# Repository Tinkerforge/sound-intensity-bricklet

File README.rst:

Sound Intensity Bricklet
========================

This repository contains the firmware source code and the hardware design
files. The documentation generator configs can be found at
https://github.com/Tinkerforge/generators

Repository Content
------------------

software/:
 * examples/: Examples for all supported languages
 * build/: Compiled files
 * src/: Source code of firmware
 * Makefile: Makefile to build project

hardware/:
 * Contains KiCad project files and additionally schematics as PDF

datasheets/:
 * Contains datasheets for sensors and complex ICs that are used

Hardware
--------

The hardware is designed with the open source EDA Suite KiCad
(http://www.kicad.org). Before you are able to open the files,
you have to install the Tinkerforge kicad-libraries
(https://github.com/Tinkerforge/kicad-libraries). You can either clone
them directly in hardware/ or clone them in a separate folder and
symlink them into hardware/
(ln -s kicad_path/kicad-libraries project_path/hardware). After that you
can open the .pro file in hardware/ with KiCad and from there view and
modify the schematics and the PCB layout.

Software
--------

If you want to do your own Brick/Bricklet firmware development we highly
recommend that you use our build environment setup script and read the
tutorial (https://www.tinkerforge.com/en/doc/Tutorials/Tutorial_Build_Environment/Tutorial.html).

To compile the C code we recommend you to install the newest GNU Arm Embedded
Toolchain (https://launchpad.net/gcc-arm-embedded/+download).
You also need to install bricklib (https://github.com/Tinkerforge/bricklib)
and brickletlib (https://github.com/Tinkerforge/brickletlib).

You can either clone it directly in software/src/ or clone it in a
separate folder and symlink it into software/src/
(ln -s bricklib_path/bricklib project_path/software/src/ and
ln -s brickletlib_path/brickletlib project_path/software/src/).
Finally make sure to have CMake installed
(http://www.cmake.org/cmake/resources/software.html).

After that you can build the firmware by invoking make in software/.
The firmware (.bin) can then be found in software/build/ and uploaded
with brickv (click button "Flashing" on start screen).

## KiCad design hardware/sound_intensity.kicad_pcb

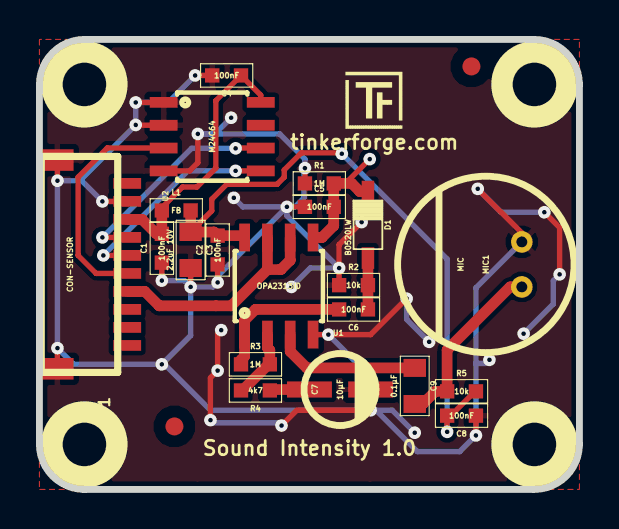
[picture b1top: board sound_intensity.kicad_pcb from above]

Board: 2 copper layers, 30.0 x 25.0 mm, 28 parts (0 on the bottom side), 14 nets.

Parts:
C1, C2, C4, C5, C6, C8: 100nF; 0603
C3: 2.2uF 10V; 0805
C7: 10µF; ELKO_43
C9: 0.1µF; 0805
D1: B0520LW; SOD-123
Fiducial_Mark: VAL**; Fiducial_Mark
Fiducial_Mark#2: VAL**; Fiducial_Mark
L1: FB; 0603
MIC1: MIC; MICRO_9_7
P1: CON-SENSOR
R1, R3: 1M; 0603
R2, R5: 10k; 0603
R4: 4k7; 0603
U1: OPA2313ID; SOIC8
U2: M24C64; SOIC8
U3, U4, U5, U6: DRILL; DRILL_NP
VAL: CE_5mm
VAL#2: WEEE_7mm

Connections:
GND: C1.1, C2.1, C3.2, C4.2, C5.1, C7.2, C8.1, MIC1.2, P1.2, P1.EP, R1.1, R2.1, U1.4, U2.1, U2.2, U2.4
unnamed: C9.2, MIC1.1, R5.1
unnamed: R3.2, R4.2, U1.2
unnamed: C7.1, R4.1
unnamed: C6.2, R3.1, U1.1
unnamed: C5.2, D1.2, R1.2, U1.5
unnamed: P1.4, U2.6
unnamed: P1.5, U2.5
unnamed: P1.6, U2.3
unnamed: P1.7, U1.6, U1.7
unnamed: C6.1, D1.1, R2.2
unnamed: C9.1, U1.3
VAA: C2.2, C3.1, C8.2, L1.2, R5.2, U1.8
VCC: C1.2, C4.1, L1.1, P1.3, U2.8

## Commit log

2013-08-20 Initial commit for Sound Intensity Bricklet (actual intensity calculation still missing)
2013-08-21 windows: Don't trigger a build in generate_makefile.bat
    Also use normal make instead of a special named one.
2013-09-16 Add examples for Sound Intensity Bricklet
2013-09-17 Fix typo
2013-09-17 Fix copy and paste fails
2013-10-15 add hardware files
2013-10-18 Fix name to fit naming convention
2013-12-19 Fix wrong length for GetDebounce packet (through brickletlib)
2014-01-06 Add static assert for BrickContext size
2014-01-10 Add Perl examples
2014-01-10 Fixed comment
2014-01-15 php: Use const for constant values
2014-02-07 Add Mathematica examples
2014-02-10 perl: fixed namespace
2014-02-12 javascript: add examples
2014-02-18 javascript: examples fixed
2014-02-20 javascript: add html exmaples
2014-02-24 javascript: port 4280, startExample()
2014-02-28 javascript: Break long lines and cleanup whitespace
2014-03-05 Add LabVIEW examples
2014-03-06 labview: Add examples in LV2010 format
2014-03-26 matlab: add examples
2014-04-02 java: Unify constants style
2014-04-02 perl: Unify print style
2014-04-17 matlab: Adapt examples to new callback style
2014-04-17 matlab: Add parentheses to make pygments happy
2014-07-15 java: Replace System.console() usage with an Eclipse compatible pattern
2014-12-02 Use ReadLine instead of ReadKey for C# example
2015-02-13 vbnet: Use ReadLine instead of ReadKey
    Because ReadKey doesn't work with a pipe as stdin on the RED Brick.
2015-03-02 windows: Stop cmake from searching for mingw32-make.exe
    Using MinGW Makefiles as generator makes cmake search for mingw32-make.exe
    which might not be installed because GnuWin32's make.exe is used instead.
2015-04-09 c: Whitespace
2015-06-24 javascript: Clean up output creation
2015-06-24 java: Remove unnecessary parentheses
2015-07-25 Make JavaScript browser example textarea readonly
2015-07-27 Cleanup C/C++, C#, Java, Python and Ruby examples
2015-07-29 Reformat changelog
2015-08-07 Use full device class name in Python examples
2015-08-12 Fix minor warnings in C/C++ examples
2015-08-13 Use correct simple value type
2015-08-14 Cleanup Delphi examples
2015-08-18 Cleanup VB.NET examples
2015-08-19 Cleanup Perl examples
2015-08-21 Use shorter print statement in Perl example
2015-09-09 Duplicate cmake call to fix bug during cmake creation
2015-09-30 Generator based example cleanup
2015-11-12 matlab: Fix callback handling for R2014a
    http://undocumentedmatlab.com/blog/matlab-callbacks-for-java-events-in-r2014a
2015-11-25 Include date and commit into changelog
2015-11-30 vbnet: Break long line
2016-05-18 c: Add missing device destroy call
2016-06-29 Whitespace
2016-07-01 Make the change UID comment more explicit
2017-04-13 csharp: Adapt example
2017-04-21 shell: Adapt example
2017-06-02 octave: Use javaObject instead of deprecated java_new
2017-11-30 Update examples from generator
2017-12-07 mathematica: Also generate .nb files
2018-01-26 c: Fine-tune printf format
2018-02-19 javascript: Close div tag correctly
2018-02-20 Cleanup KiCad libraries config
    Ensure LibDir=kicad-libraries and LibName1=tinkerforge.
    Remove special library.
2018-05-24 perl: Use strict in examples
2018-07-11 Add Makefile with docker support
2018-07-11 Remove obsolete generate_makefile scripts
2018-07-11 Update directory structure and build instructions
2018-11-06 Add rust examples
2018-11-07 rust: Accept host names for ip connection, fix naming inconsistencies
2018-11-07 rust: Rename callback receivers.
2018-12-14 Add go examples.
2018-12-18 go: Change import path.
2018-12-18 go: Change import path again.
2018-12-20 rust: Reformat examples.
2019-01-24 mqtt: Add examples.
2019-01-24 mqtt: Fix example header.
2019-01-24 mqtt: Remove executable bit in example permissions.
2019-01-24 go: Minor example fixes.
2019-01-24 mqtt: Minor example fixes.
2019-03-28 mqtt: Fix whitespace.
2019-08-22 c: Adapt to bindings changes
2020-01-13 examples: Use python3 input instead of python2 raw_input.
2020-01-13 examples: mqtt: Remove trailing whitespace.
2020-04-14 mqtt: Fix device name format
2021-10-25 Update KiCad link
    https://www.kicad.org/blog/2021/10/Avoid-links-to-former-kicad-domain/
2022-05-10 go: Fix format string
2022-07-06 Add license files.

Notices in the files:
hardware/sound_intensity.kicad_pcb:
Licensed under CERN OHL v.1.1
Copyright (©) 2013, B.Nordmeyer
Copyright Tinkerforge GmbH 2013.
This documentation describes Open Hardware and is licensed under the
CERN OHL v. 1.1.
